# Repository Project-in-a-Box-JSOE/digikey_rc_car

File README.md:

# SYWMI_RC_Car

**A Digikey collaborated project**
> Project documentation [@Maker.io](https://www.digikey.com/en/maker/profiles/b3c9555ffd7248bcb833dc392372bf2a)<br />
> More about [Project in a Box](https://pibucsd.org/)

## Overview
Create your own remote controlled (RC) car from scratch with Project in a Box (PiB)! This project is jammed packed with ECE concepts, such as communications, hardware and electronic prototyping, CAD, and programming.

## BOM
For simplicity, we will split the project's BOM into three:
- Remote
- Car (Electronics)
- Car (Hardware)

Find them [here](BOM.pdf)

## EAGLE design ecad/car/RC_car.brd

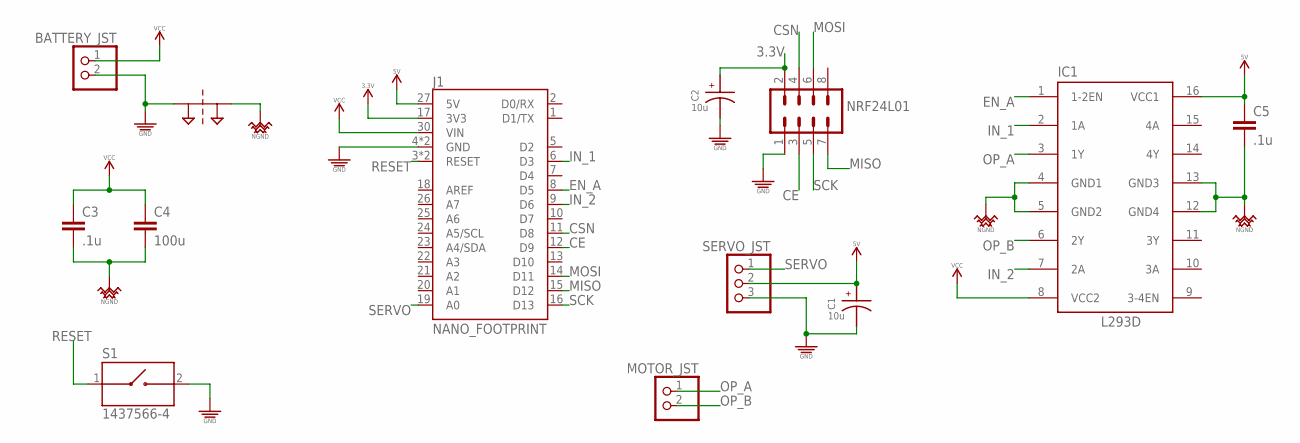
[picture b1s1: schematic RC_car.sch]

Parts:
BATTERY_JST: PINHD-1X2; 1X02
C1, C2: 10u; CAPPRD200W50D550H1250
C3, C5: .1u; C2.5-3
C4: 100u; C2.5-3
IC1: L293D; DIL16
J1: NANO_FOOTPRINT; NANO
MOTOR_JST: PINHD-1X2; 1X02
NET_BRIDGE1: NET_BRIDGE
NRF24L01: MA04-2
S1: 1437566-4; SW_1437566-4
SERVO_JST: PINHD-1X3; 1X03

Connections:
3.3V: C2.1, J1.17 (3V3), NRF24L01.2
5V: C1.1, C5.1, IC1.16 (VCC1), J1.27 (5V), SERVO_JST.2
CE: J1.12 (D9), NRF24L01.3
CSN: J1.11 (D8), NRF24L01.4
EN_A: IC1.1 (1-2EN), J1.8 (D5)
GND: BATTERY_JST.2, C1.2, C2.2, J1.4 (GND), J1.29 (GND), NET_BRIDGE1.P$1, NRF24L01.1, S1.2, SERVO_JST.3
IN_1: IC1.2 (1A), J1.6 (D3)
IN_2: IC1.7 (2A), J1.9 (D6)
MISO: J1.15 (D12), NRF24L01.7
MOSI: J1.14 (D11), NRF24L01.6
NGND: C3.2, C4.2, C5.2, IC1.4 (GND1), IC1.5 (GND2), IC1.12 (GND4), IC1.13 (GND3), NET_BRIDGE1.P$2
OP_A: IC1.3 (1Y), MOTOR_JST.1
OP_B: IC1.6 (2Y), MOTOR_JST.2
RESET: J1.3 (RESET), J1.28 (RESET), S1.1
SCK: J1.16 (D13), NRF24L01.5
SERVO: J1.19 (A0), SERVO_JST.1
VCC: BATTERY_JST.1, C3.1, C4.1, IC1.8 (VCC2), J1.30 (VIN)

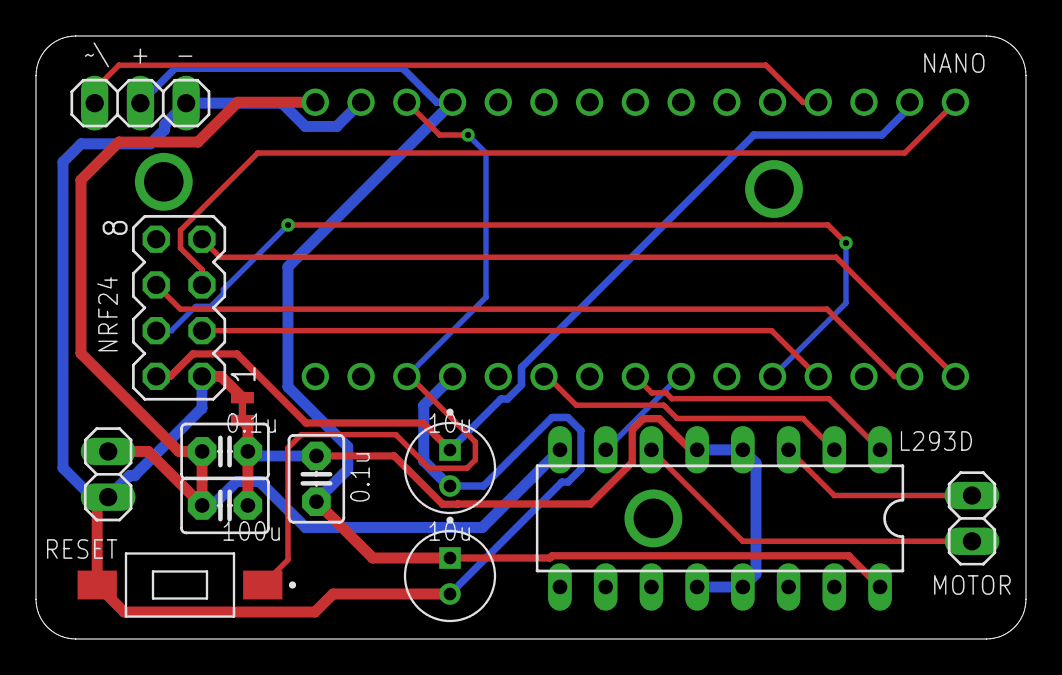
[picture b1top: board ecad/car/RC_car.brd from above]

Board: 2 copper layers, 55.0 x 33.5 mm, 13 parts (0 on the bottom side), 17 nets.

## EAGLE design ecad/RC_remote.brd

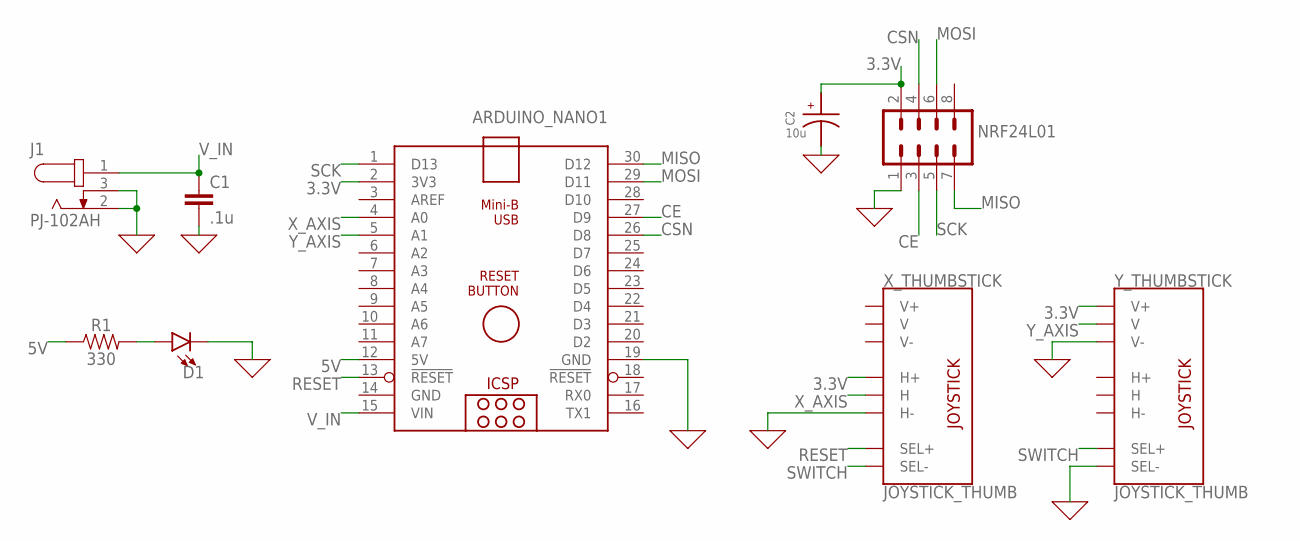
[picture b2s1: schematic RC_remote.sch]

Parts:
ARDUINO_NANO1: ARDUINO_NANO
C1: .1u; C2.5-3
C2: 10u; CAPPRD200W50D550H1250
D1: LED5MM; LED_5MM
J1: PJ-102AH; CUI_PJ-102AH
NRF24L01: MA04-2
R1: 330; AXIAL-0.3
X_THUMBSTICK: JOYSTICK_THUMB; JOYSTICK
Y_THUMBSTICK: JOYSTICK_THUMB; JOYSTICK

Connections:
0: ARDUINO_NANO1.19 (GND), C1.2, C2.2, D1.K (C), J1.2, J1.3, NRF24L01.1, X_THUMBSTICK.H3 (H-), Y_THUMBSTICK.B2A (SEL-), Y_THUMBSTICK.V3 (V-)
3.3V: ARDUINO_NANO1.2 (3V3), C2.1, NRF24L01.2, X_THUMBSTICK.H1 (H+), Y_THUMBSTICK.V1 (V+)
5V: ARDUINO_NANO1.12 (5V), R1.P$1 (1)
CE: ARDUINO_NANO1.27 (D9), NRF24L01.3
CSN: ARDUINO_NANO1.26 (D8), NRF24L01.4
GND: ARDUINO_NANO1.14 (GND)
MISO: ARDUINO_NANO1.30 (D12), NRF24L01.7
MOSI: ARDUINO_NANO1.29 (D11), NRF24L01.6
unnamed: D1.A, R1.P$2 (2)
RESET: ARDUINO_NANO1.13 (!RESET), X_THUMBSTICK.B1A (SEL+)
SCK: ARDUINO_NANO1.1 (D13), NRF24L01.5
SWITCH: X_THUMBSTICK.B2A (SEL-), Y_THUMBSTICK.B1A (SEL+)
V_IN: ARDUINO_NANO1.15 (VIN), C1.1, J1.1
X_AXIS: ARDUINO_NANO1.4 (A0), X_THUMBSTICK.H2 (H)
Y_AXIS: ARDUINO_NANO1.5 (A1), Y_THUMBSTICK.V2 (V)

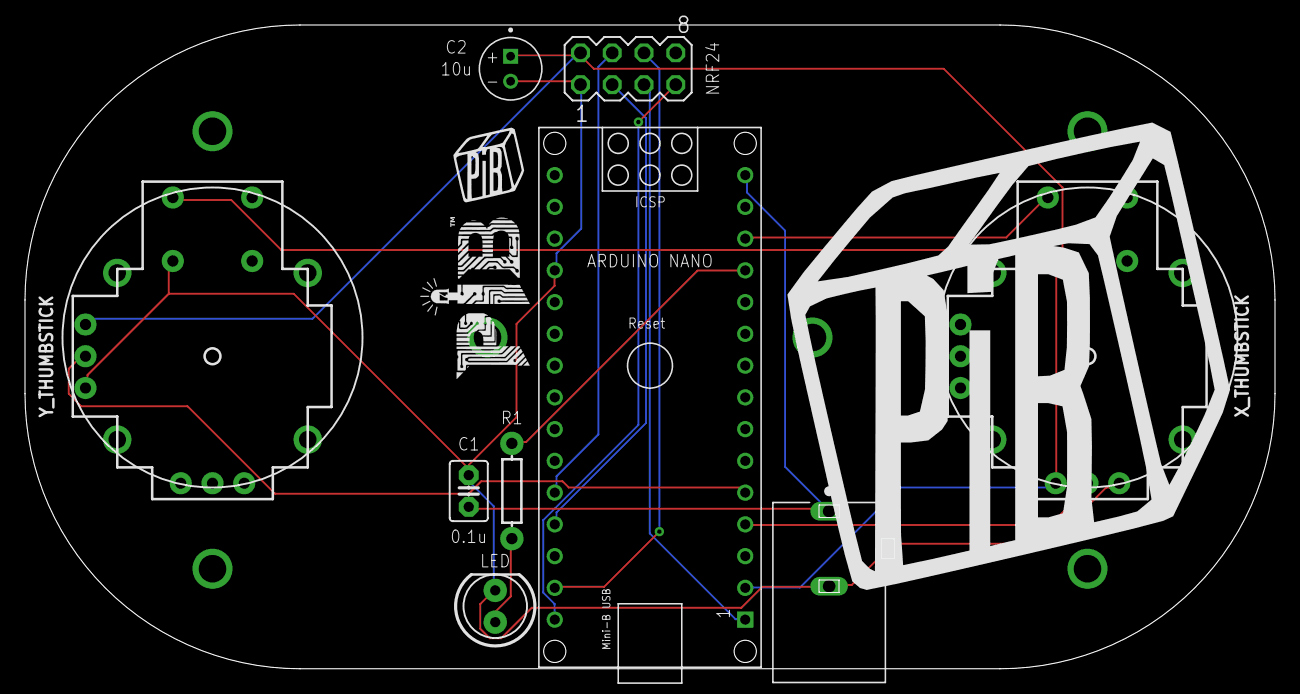
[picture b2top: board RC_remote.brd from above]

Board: 2 copper layers, 100.0 x 51.5 mm, 13 parts (1 on the bottom side), 14 nets.

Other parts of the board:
U$1: PIB_LOGO_40MM
U$2: PIB-LOGO
U$3, U$4: PIB_LOGO_10MM

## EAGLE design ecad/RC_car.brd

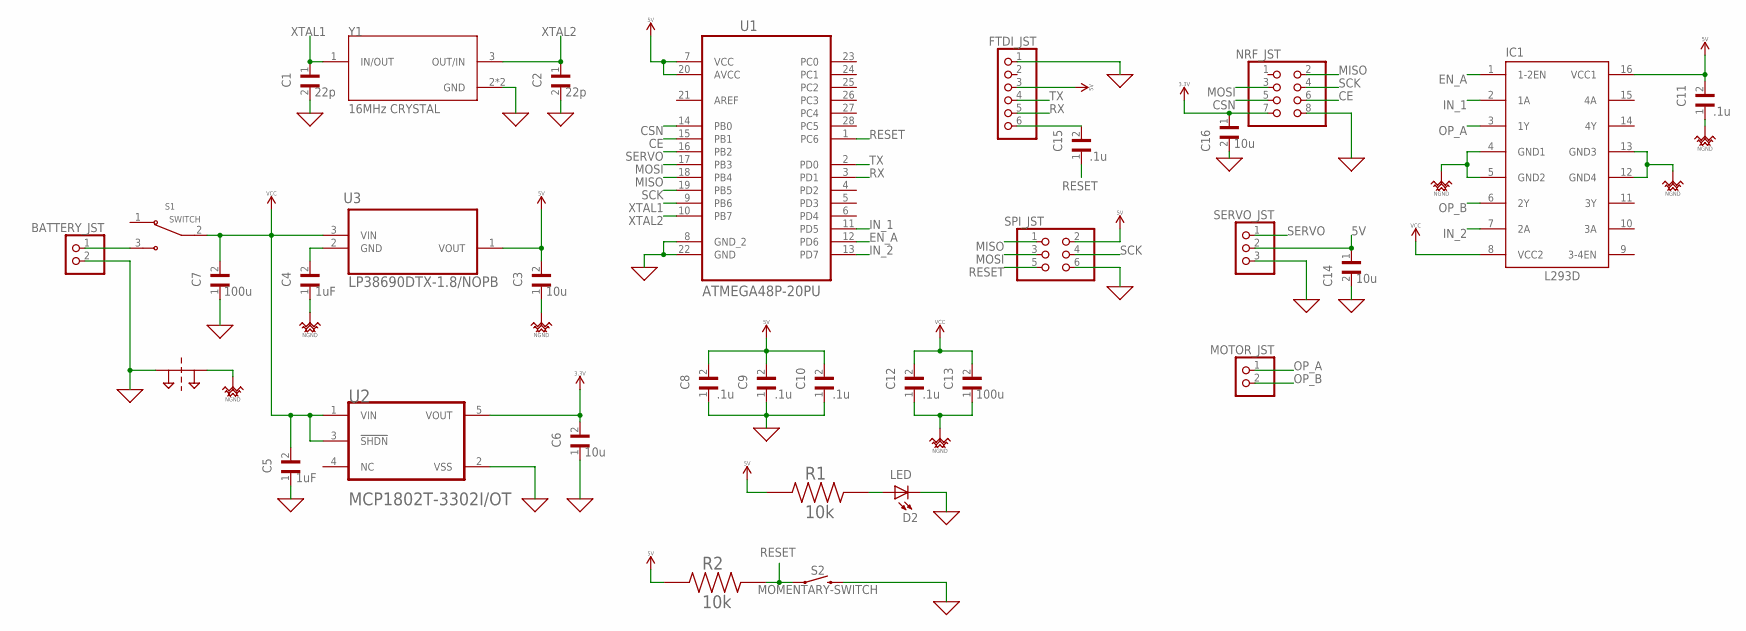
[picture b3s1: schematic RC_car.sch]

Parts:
BATTERY_JST: PINHD-1X2; 1X02
C1, C2: 22p; CAPC2012X140N
C3, C6: 10u; CAPC2013X95N
C4, C5: 1uF; CAPC2012X70N
C7, C13: 100u; CAPC3225X280N
C8, C9, C10, C11, C12, C15: .1u; CAPC2012X140N
C14, C16: 10u; CAPC1608X90
D2: LED; DIOC200X125X110
FTDI_JST: PINHD-1X6; 1X06
IC1: L293D; DIL16
MOTOR_JST: PINHD-1X2; 1X02
NET_BRIDGE1: NET_BRIDGE
NRF_JST: PINHD-2X4; 2X04
R1, R2: 10k; RESC2012X60N
S1: SWITCH; SW_500SSP1S2M2QEA
S2: MOMENTARY-SWITCH; TACTILE_SWITCH_PTH_6.0MM
SERVO_JST: PINHD-1X3; 1X03
SPI_JST: PINHD-2X3; 2X03
U1: ATMEGA48P-20PU; DIP254P762X457-28
U2: MICROCHIP_MCP1802T-3302I-OTMICROCHIP_MCP1802T-330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; MICROCHIP_MCP1802T-3302I-OT_0
U3: LP38690DTX-1.8/NOPB; TO228P1042X238-3N
Y1: 16MHz CRYSTAL; XTAL_ECS-160-12-33-AGN-TR

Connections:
0: BATTERY_JST.2, C1.2, C2.2, C5.1, C6.1, C7.1, C8.1, C9.1, C10.1, C14.2, C16.2, D2.-, FTDI_JST.1, NET_BRIDGE1.P$1, NRF_JST.8, S2.3 (2), SERVO_JST.3, SPI_JST.6, U1.8 (GND_2), U1.22 (GND), U2.2 (VSS), Y1.2 (GND), Y1.4 (GND)
3.3V: C6.2, C16.1, NRF_JST.7, U2.5 (VOUT)
5V: C3.2, C8.2, C9.2, C10.2, C11.2, C14.1, FTDI_JST.3, IC1.16 (VCC1), R1.1, R2.1, SERVO_JST.2, SPI_JST.2, U1.7 (VCC), U1.20 (AVCC), U3.1 (VOUT)
CE: NRF_JST.6, U1.15 (PB1)
CSN: NRF_JST.5, U1.14 (PB0)
EN_A: IC1.1 (1-2EN), U1.12 (PD6)
IN_1: IC1.2 (1A), U1.11 (PD5)
IN_2: IC1.7 (2A), U1.13 (PD7)
MISO: NRF_JST.2, SPI_JST.1, U1.18 (PB4)
MOSI: NRF_JST.3, SPI_JST.3, U1.17 (PB3)
unnamed: BATTERY_JST.1, S1.3 (NO)
unnamed: C4.2, U3.2 (GND)
unnamed: C15.2, FTDI_JST.6
unnamed: D2.+, R1.2
NGND: C3.1, C4.1, C11.1, C12.1, C13.1, IC1.4 (GND1), IC1.5 (GND2), IC1.12 (GND4), IC1.13 (GND3), NET_BRIDGE1.P$2
OP_A: IC1.3 (1Y), MOTOR_JST.1
OP_B: IC1.6 (2Y), MOTOR_JST.2
RESET: C15.1, R2.2, S2.1, SPI_JST.5, U1.1 (PC6)
RX: FTDI_JST.5, U1.3 (PD1)
SCK: NRF_JST.4, SPI_JST.4, U1.19 (PB5)
SERVO: SERVO_JST.1, U1.16 (PB2)
TX: FTDI_JST.4, U1.2 (PD0)
VCC: C5.2, C7.2, C12.2, C13.2, IC1.8 (VCC2), S1.2 (COM), U2.1 (VIN), U2.3 (!SHDN!), U3.3 (VIN)
XTAL1: C1.1, U1.9 (PB6), Y1.1 (IN/OUT)
XTAL2: C2.1, U1.10 (PB7), Y1.3 (OUT/IN)

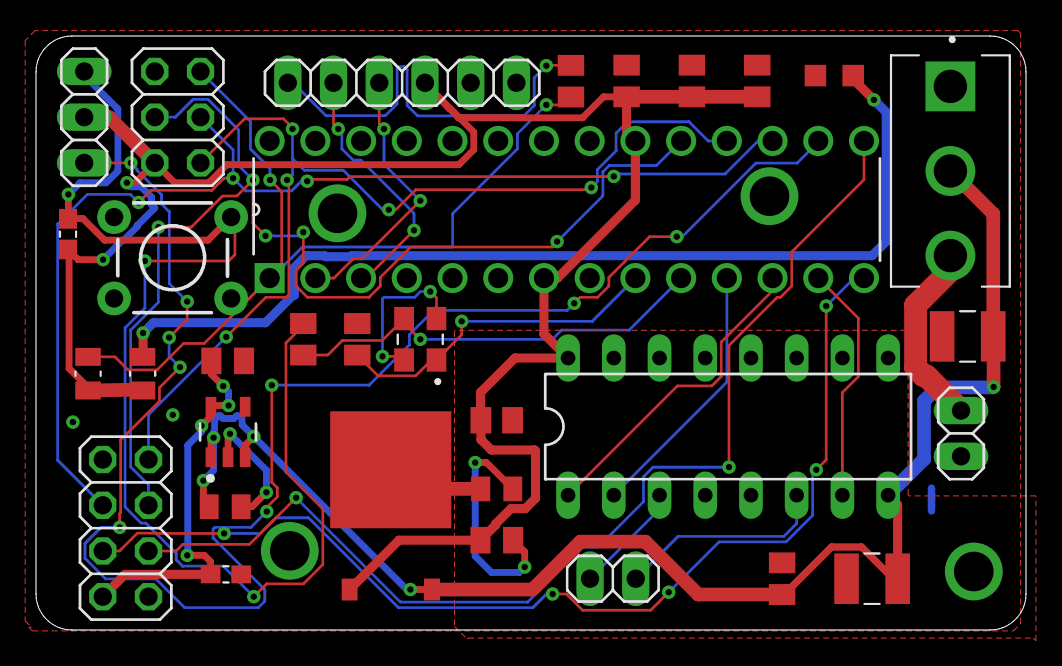
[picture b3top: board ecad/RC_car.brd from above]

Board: 2 copper layers, 55.0 x 33.0 mm, 33 parts (1 on the bottom side), 25 nets.

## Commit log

2021-12-22 RF example code
2021-12-22 gitignore update
2021-12-22 DS store removed
2021-12-22 RF example update
2021-12-22 joystick example update
2021-12-22 motor driver example update
2021-12-23 rf24 library deleted
2021-12-23 remove DS_Store
2021-12-23 motor driver and servo integ example
2021-12-23 fixed incorrect rf24 library
2021-12-23 new complete remote and car code
2021-12-23 compeleted schematic
2021-12-24 debugging changes
2021-12-24 modified isp programmer code
2021-12-28 eagle lib
2022-01-03 ecad remote
2022-01-03 ecad update
2022-01-04 ecad car
2022-01-04 ecad doc
2022-01-25 v1 eagle files
2022-02-23 laser cut files
2022-04-29 print files
2022-05-14 nano rc car
2022-05-14 pcb step model
2022-05-15 flipped header
2022-08-03 remove outdated files
2022-08-03 ecad cleanup
2022-08-03 updated mcad files
2022-08-04 maker.io link
2022-08-04 readme update
2022-08-04 remote code update
2022-08-06 additional readmes
2022-08-21 static bom link
2022-08-23 atmega design

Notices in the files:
parts and their libraries:
SparkFun-Switches: Licensing: Creative Commons ShareAlike 4.0 International - https://creativecommons.org/licenses/by-sa/4.0
